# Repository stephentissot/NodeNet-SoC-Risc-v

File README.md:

# NodeNet SoC Risc-v — Colorlight i9 Multi-Node Embedded System

A complete RISC-V System-on-Chip (SoC) design for the Colorlight i9 FPGA board, featuring a PicoRV32 processor, Wishbone bus interconnect, persistent SPI flash storage, I2C peripherals, distributed RS485 multi-node communication via the NodeNet485 protocol, and a PLC runtime ready for relocatable object-file deployment.

## Overview

This project demonstrates a scalable embedded systems design on a cost-effective FPGA:
- **Processor**: PicoRV32 (32-bit RISC-V, bare-metal)
- **Clock**: 25 MHz
- **Memory**: 64 KiB ROM (stage0 bootloader) + 64 KiB RAM (stack/variables) + 8 MB SDRAM (runtime application/external data)
- **Peripherals**: D2 LED GPIO, RJ45 LED pulse controllers (`wb_led`), UART1 Modbus RTU master (`wb_modbus_master`), RS485 NodeNet485, I2C master, SDRAM controller
- **Communication**: NodeNet485 @ 1 Mb/s over RS-485 (multi-node capable)
- **Firmware**: C++17, bare-metal, newlib-nano
- **Validated boot path**: stage0 in ROM validates an image header in SPI flash, copies the payload to SDRAM, checks CRC, then jumps to the application entry point
- **Validated SDRAM path**: full firmware execution from SDRAM, 32-bit accesses, partial Wishbone writes, linker-placed `SDRAM_DATA` variables, and scratch-area self-tests

Current project status:
- **PLC Ready** with **V0 basic ISA**
- runtime point catalog with `pointDefsReq` / `pointStatesReq` browsing and pagination
- relocatable `objectFileV1` PLC upload, firmware-side link/load, linked-bytecode readback, and object-file readback
- 16 PLC slots with reboot persistence in the raw PLC flash package and automatic restore after boot
- OLED boot progress screen plus post-boot slot status screen
- ESP32 SPI coprocessor for local web API is in progress on the current branch; the shared SPI link, snapshot bootstrap, incremental state updates, and web UI runtime path are now working together on hardware, while broader validation and the MQTT bridge remain pending

## Features

### NodeNet PLC
- NodeNet PLC catalog browsing supports `pointDefsReq` and `pointStatesReq` with hierarchical paths of the form `deviceId.feature.pointId`.
- Point definitions can be created or updated with `pointUpsert`, and removed with `pointDelete`.
- Modbus-backed points are polled by the PLC runtime and exposed through the same NodeNet command surface.
- The PLC runtime publishes a shared SDRAM descriptor/value/status map, and PLC VM writes are consumed through the runtime write queue.
- Generic PLC deployment uses relocatable `objectFileV1` artifacts; the built-in `plcLoadReq` mirror helper remains available for fast validation.

PLC feature summary:
- Main feature status: PLC Ready with V0 basic ISA
- Runtime architecture: shared SDRAM PLC ABI, point runtime descriptors, value/status windows, slot loader/linker, persistent flash package restore at boot
- Deployment model: host builds relocatable `objectFileV1`, firmware links it against the live point catalog, loads it into one of 16 slots, and can persist the slot set for reboot restore
- Operating surface: NodeNet browse/update commands for point definitions and point states, PLC slot control/status points, raw PLC upload flow, linked-bytecode readback, and original object-file readback

PLC documentation index:
- Command surface and JSON examples: [README_NODENET_PLC_COMMANDS.md](README_NODENET_PLC_COMMANDS.md)
- PLC VM runtime architecture and ABI: [Documentation/plc_vm_spec_v1.md](Documentation/plc_vm_spec_v1.md)
- PLC assembly / object-file format: [Documentation/plc_assembly_spec_v1.md](Documentation/plc_assembly_spec_v1.md)
- ESP32 SPI bridge pinout and PlatformIO notes: [Documentation/esp32_spi_bridge_notes.md](Documentation/esp32_spi_bridge_notes.md)
- Firmware runtime and flash layout: [src/firmware/README.md](src/firmware/README.md)
- Stage0 boot flow and runtime handoff: [src/firmware/README_BOOT.md](src/firmware/README_BOOT.md)
- NodeNet transport details: [src/wbDevices/README_NODENET.md](src/wbDevices/README_NODENET.md)
- SPI flash persistence details: [src/wbDevices/README_FLASH.md](src/wbDevices/README_FLASH.md)
- Desktop PLC object-file tooling: [tools/BigSisterNodeNet.Plc/README.md](tools/BigSisterNodeNet.Plc/README.md)

### NodeNet Validation Snapshot (2026-08-20)
- Automatic heartbeat in HDL validated on hardware at ~10 s period.
- RX to local address validated (message accepted and decoded).
- TX path validated end-to-end.
- Runtime baud operation validated at both 115200 and 1 Mb/s.
- RX metadata is propagated end-to-end (`src`, `dst`, `broadcast`, `len`).
- Distinct PicoRV32 IRQs exist for broadcast vs unicast RX and are consumed through firmware callbacks.
- ROM stage0 now forwards the fixed IRQ vector at `0x00000004` to the SDRAM app IRQ entry.

### FlashDB Validation Snapshot (2026-08-13)
- Flash low-level test passes at boot (`[FLASH] LowLevel PASS`).
- FlashDB initialization passes (`[FDB] Ready`).
- Boot counter write path passes (`[FDB] boot cnt updated`).

### Hardware
- **Wishbone B.4 Bus** interconnect with 32-bit data, 32-bit address
- **PicoRV32 Core**: Open-source RISC-V ISA, ~6K LUT footprint
- **Memory Map**:
  - `0x00000000–0x0000FFFF`: 64 KiB boot ROM (stage0 bootloader)
  - `0x00010000–0x0001FFFF`: 64 KiB RAM (stack, BSS, heap)
  - `0x10000000`: D2 LED GPIO (1-bit output)
  - `0x10000004`: RJ45 LED0 (`wb_led` one-shot pulse)
  - `0x10000008`: RJ45 LED1 (`wb_led` one-shot pulse)
  - `0x10004000`: UART1 Modbus RTU master (`wb_modbus_master`)
  - `0x10005000`: I2C0 master (8 registers @ 4-byte stride)
  - `0x10006000`: NodeNet485 RS-485 mailbox (8 registers, 1 Mb/s)
  - `0x20000000–0x207FFFFF`: 8 MB SDRAM (runtime application image / framebuffer / logs)

### Peripherals
- **NodeNet485 Module** (`wb_nodenet.sv`):
  - Multi-node RS-485 communication protocol
  - Baud rate: runtime divisor (validated at 115200 and 1 Mb/s)
  - HDLC-style framing with parity bits and CRC
  - Mailbox-based Wishbone interface for TX/RX messages
  - Internal message buffering (no external SDRAM FIFO usage)
  - Anti-collision backoff (address-based delay)
  - Periodic heartbeat for node discovery
  - Priority-based transmission (LOW/NORMAL/HIGH)
  - Full C++ firmware API in `src/firmware/lib/nodenet/nodenet.h`
  - Supports unicast, broadcast, and heartbeat messages
  - Supports callback-driven broadcast / unicast reception on PicoRV32 IRQs
  - RX decode error reporting and TX scheduling status
  - Wishbone register interface (0x10006000)

- **I2C Module** (`wb_i2c.sv`):
  - Wraps Alex Forencich's `i2c_master_wbs_16` core
  - Hardware command + write + read FIFOs (32 entries each)
  - Configurable speed (default 100 kHz, up to 400 kHz @ 25 MHz)
  - Drives SCL/SDA open-drain (external 4.7 kΩ pullup required)
  - Wishbone address: 0x10005000

- **Modbus Master Module** (`src/modbus/wb_modbus_master.sv`):
  - Wishbone Modbus RTU master transaction engine
  - Uses shared `uart_simple.sv` UART core for wire-level TX/RX
  - Hardware-managed CRC16 (TX generation + RX validation)
  - Hardware-managed RTU frame gap detection (inter-frame silence)
  - Retries, timeout, and status/error flags exposed through MMIO
  - Firmware API in `src/firmware/lib/modbus/ModbusMaster.{h,cpp}`
  - Wishbone address: 0x10004000

- **SPI Flash Module** (`wb_flash.sv`, `spi_master.sv`):
  - Wishbone interface to on-board SPI flash (W25Q64, 8 MB)
  - Memory layout: 2 MB boot config (protected) + 12 KB point catalog + 4 KB compatibility gap + 128 KB PLC package + 124 KB FlashDB KV + 4 KB self-test scratch + app data
  - C++ firmware uses low-level page/sector API (`Flash`) plus FlashDB wrapper (`flashdb_port`)
  - Exposes the factory-programmed 64-bit Winbond UID as a stable ASCII device ID
  - Boot region protection: firmware rejects writes/erases to 0x000000–0x1FFFFF
  - Point catalog storage at 0x200000–0x202FFF (12 KB, 3 sectors)
  - Compatibility gap at 0x203000–0x203FFF (4 KB)
  - Persistent PLC package at 0x204000–0x223FFF (128 KB)
  - FlashDB KV partition at 0x224000–0x242FFF (124 KB)
  - Flash low-level self-test scratch at 0x243000–0x243FFF (4 KB)
  - Wishbone address: 0x10007000
  - See [src/wbDevices/README_FLASH.md](src/wbDevices/README_FLASH.md) for details
### Firmware
- **C++17 bare-metal** (`firmware/main.cpp`):
  - Compiled with `riscv-none-elf-g++` — no Arduino, no OS
  - `newlib-nano` provides `memcpy`/`strlen`/etc.
  - Dead code elimination (`-ffunction-sections -Wl,--gc-sections`)
  - Global C++ constructors called in `start.S` via `.init_array`
  - Final runtime image is linked for SDRAM via `link_app_sdram.ld`
  - Loaded by ROM-resident `boot_stage0` from SPI flash offset `0x244000`
  - Includes ArduinoJson 7 in freestanding mode, with an optional SDRAM-backed allocator for large JSON payloads
  - **NodeNet485 callback flow**: receives broadcast/unicast events through IRQ callbacks and defers heavy work to the main loop
  - D2 activity heartbeat: non-blocking software toggle every 500 ms

- **External SDRAM bring-up**:
  - Cold boot initialization now follows the generated LiteDRAM DFII sequence before the SDRAM user port is released
  - Firmware should still call `sdram_wait_ready()` before touching `SDRAM_DATA` objects or the JSON SDRAM pool

- See [src/firmware/README.md](src/firmware/README.md) for full peripheral usage guide.
- See [src/wbDevices/README_NODENET.md](src/wbDevices/README_NODENET.md) for protocol details.
- See [src/modbus/README.md](src/modbus/README.md) for Modbus RTU master details.
- See [src/wbDevices/README_FLASH.md](src/wbDevices/README_FLASH.md) for flash UID and device ID details.

## Building

### Prerequisites
- Yosys (synthesis)
- NextPNR (place & route)
- ecppack (bitstream generation)
- RISC-V GCC toolchain (`riscv-none-elf-gcc` ≥ 12, with C++ support)
- Make

> **After cloning**, fetch the u8g2 submodule:
> ```bash
> git submodule update --init
> ```

### Build Steps

```bash
# Full build (firmware + FPGA)
make all

# Stage0 bootloader only (ROM image)
make firmware-bootloader

# Alias: same stage0 ROM build as above
make firmware-build

# Build stage0 application image (SDRAM payload + header in SPI flash format)
make firmware-image

# SDRAM application ELF only
make -C src/firmware firmware-app-build

# Program firmware payload only in SPI flash (no FPGA rebuild)
make flash-fw

# If bootloader ROM startup / IRQ forwarding changed, reload the FPGA image too
make ram

# Optional: enforce openFPGALoader verify as fatal
make FW_STRICT_VERIFY=1 flash-fw

# Generate boot robustness test images (missing/size/crc fault injections)
make firmware-image-tests

# Run boot robustness fault scenarios
make flash-fw-test-missing
make flash-fw-test-crc
make flash-fw-test-size

# Firmware-only FPGA RAM update (ecpbram patch, fallback to make ram if needed)
make ram-fw

# Boot fault campaign checklist and expected blink codes
# See TEST.md

# FPGA synthesis only (requires pre-built firmware)
make

# Clean all artifacts
make clean

# Program FPGA SRAM (volatile)
make ram

# Program SPI flash (persistent, includes unlock during write)
make flash

# Manual flash protection control
make unlock-flash
make lock-flash
```

`make firmware-build` / `make firmware-bootloader` print stage0 ROM size telemetry on each build:
- ELF text/data/bss
- RAM usage (`.data + .bss`)
- HEX file size and payload bytes
- ROM usage (`payload / ROM_BYTES`, in %)

If payload exceeds ROM capacity, build stops with an explicit error.

CPU profile note:
- Default build is configured in fast mode for PicoRV32 in [src/top.sv](src/top.sv) with:
  - `.BARREL_SHIFTER(1)`
  - `.ENABLE_FAST_MUL(1)`
  - `.ENABLE_DIV(1)`
- To switch back to the normal/smaller CPU profile, set those three parameters to `0` in [src/top.sv](src/top.sv) and rebuild (`make clean; make`).

If OpenOCD flash programming fails on your setup, you can switch the flash
targets in `Makefile` to ecpdap. Reference commands:

```make
# ecpdap fallback examples (Colorlight i5/i9 style headers)
# flash:
# 	ecpdap flash unprotect
# 	ecpdap flash write build/top.config
#
# unlock-flash:
# 	ecpdap flash unprotect
#
# lock-flash:
# 	ecpdap flash protect
```

**Output**:
- `src/firmware/build/boot_stage0.hex` – Stage0 bootloader image (loaded into ROM, includes IRQ forward stub to the SDRAM app)
- `src/firmware/build/nodenet_riscv_app.img` – SDRAM app payload with stage0 header (written in SPI flash at `0x244000`)
- `build/top.bit` – FPGA bitstream (~300 KB)
- `build/top.json` – Netlist (debug/inspection)

## Memory Layout

```
Address Range               Size      Purpose
────────────────────────────────────────────────────────────
0x00000000–0x0000FFFF     64 KiB   Boot ROM (stage0 bootloader)
0x00010000–0x0001FFFF     64 KiB   RAM (stack, BSS, heap)
────────────────────────────────────────────────────────────
0x10000000                4 B      D2 LED GPIO (bit [0] = LED output)
0x10000004                4 B      RJ45 LED0 (`wb_led` control/status)
0x10000008                4 B      RJ45 LED1 (`wb_led` control/status)
0x10004000                32 B     UART1 Modbus RTU master (`wb_modbus_master`)
0x10005000                32 B     I2C0 master (8 regs @ 4-byte stride)
0x10006000–0x1000601F     32 B     NodeNet485 mailbox + LED config (RS485, 1 Mb/s)
0x10007000                32 B     SPI Flash controller (W25Q64)
────────────────────────────────────────────────────────────
0x20000000–0x207FFFFF     8 MB     SDRAM — Runtime app image + large buffers/logs
────────────────────────────────────────────────────────────
0x00000000–0x1FFFFF       2 MB     SPI Flash — FPGA boot config (PROTECTED)
0x200000-0x202FFF         12 KB    SPI Flash — Point catalog
0x203000-0x203FFF         4 KB     SPI Flash — Compatibility gap / reserved
0x204000-0x223FFF         128 KB   SPI Flash — Persistent PLC package
0x224000-0x242FFF         124 KB   SPI Flash — FlashDB KV partition
0x243000-0x243FFF         4 KB     SPI Flash — Flash low-level self-test scratch
0x244000–0x7FFFFF         5.73 MB  SPI Flash — Stage0 application image slot
```

## Boot Flow

1. FPGA configuration loads the SoC bitstream and the `wb_rom` contents containing `boot_stage0`.
2. Stage0 starts from `0x00000000`, initializes required peripherals, and reads the application header from SPI flash offset `0x244000`.
3. Stage0 validates header fields and CRCs, copies the application payload into SDRAM at `0x20000000`, then jumps to the image entry point.
4. PicoRV32 IRQ entry remains fixed at `0x00000004`; the ROM image forwards that vector to the SDRAM application IRQ entry at `0x20000004`.
5. The runtime firmware executes entirely from SDRAM, while SPI flash remains available for parameter storage, FlashDB, and firmware updates.
6. SDRAM self-tests used by the runtime stay inside a reserved scratch area so they do not overwrite the executing image.

## Device Pinout

### RS485 (NodeNet485 Protocol)
- **Pins**: G5 (RX), D16 (TX)
- **Baud Rate**: 1 Mb/s (fixed, configurable via UART parameter)
- **Protocol**: Multi-node RS-485 with HDLC framing, anti-collision, heartbeat
- **Transceiver**: Any RS-485 module with auto-switching (MAX485, SN65HVD11, etc.)
- **Multi-Node**: Up to 20 nodes on shared bus with address-based scheduling
- **Features**: Parity-encoded payload (2x expansion), XOR CRC, priority levels (LOW/NORMAL/HIGH), heartbeat
- **Connector topology**: 2x RJ45 in daisy-chain (IN/OUT), wired pin-to-pin between connectors

NodeNet RJ45 pinout (both connectors):

| RJ45 Pin | Signal |
|---|---|
| 1 | +12V |
| 2 | +12V |
| 3 | RS485 A |
| 4 | GND |
| 5 | GND |
| 6 | RS485 B |
| 7 | GND |
| 8 | GND |

### I2C (D18/D17 pins)
- **SCL**: D18
- **SDA**: D17
- Requires external 4.7 kΩ pullup resistors to 3.3 V on both lines
- Compatible with any I2C device: OLED, sensors, ADC, GPIO expanders…

### GPIO
- **D2 LED**: GPIO output at 0x10000000 (bit [0] = LED state)

### RJ45 LEDs (`wb_led`)
- **LED0 (F5)**: `0x10000004`
- **LED1 (E6)**: `0x10000008`
- Active-low wiring policy: GPIO high = LED OFF, GPIO low = LED ON.
- LPF enables pull-up on these pins for deterministic OFF level during startup.
- Write command bit0 triggers a non-blocking pulse (duration can be overridden by firmware).
- RJ45 LEDs are available through `wb_led` and can be used by application firmware when needed.

### NodeNet Activity LEDs (100% hardware)
- **RX activity LED (E5, green)**: default ON, pulses OFF when a valid frame is received.
- **TX activity LED (F4, orange)**: pulses ON when a transmission is queued.
- Active-low with pull-up: idle/high keeps LED OFF unless logic drives low.
- Blink duration is configured by firmware through NodeNet register `0x1000601C` (milliseconds).

### SPI Flash (W25Q64)
- **Pins**: R2 (CS), W2 (MOSI), V2 (MISO)
- **Clock**: Generated internally (10 MHz typical, no GPIO pin)
- **Capacity**: 8 MB (2 MB boot + 16 KB params + 256 KB FlashDB KV + ~5.73 MB app)
- **Boot Protection**: Firmware API rejects writes to 0x000000–0x1FFFFF
- **Parameter Region**: 0x200000–0x203FFF (raw/scratch area)
- **FlashDB KV Region**: 0x204000–0x243FFF (`nodenet_kv` partition)

## Firmware Examples

See **[src/firmware/README.md](src/firmware/README.md)** for a full guide with code examples for every peripheral.

### Quick-start: UART1 Modbus RTU master
```cpp
#include "ModbusMaster.h"

constexpr uint32_t MODBUS1_BASE = 0x10004000u;
constexpr uint8_t MODBUS_SLAVE = 0x01u;
ModbusMaster modbus1(MODBUS1_BASE);

int main() {
  modbus1.begin(9600, 500, 2);
  modbus1.setInterframeCharsQ1(14);

  uint16_t version = 0;
  if (modbus1.readHoldingRegisters(MODBUS_SLAVE, 0x8000, 1, &version)) {
    // 0x0064 => V1.00
  }

  for (;;) {
    // Toggle channel 1 (coil address 0)
    (void)modbus1.writeSingleCoil(MODBUS_SLAVE, 0x0000, true);
  }
}
```

### Quick-start: NodeNet echo
```cpp
#include <stdint.h>
#include "nodenet.h"

#define LED          (*(volatile uint32_t*)0x10000000)
constexpr uint32_t NODENET0_BASE = 0x10006000u;

int main() {
  NodeNet myNodeNet(NODENET0_BASE, 0x01, NODENET_PRIORITY_NORMAL, 200);
  for (;;) {
    if (myNodeNet.HasMessage()) {
      NodeNetMessage msg = myNodeNet.ReadMessage();
      if (msg.src_addr != 0) {
        myNodeNet.Send(msg.src_addr, msg.data, msg.len);
      }
      NodeNet::FreeMessage(msg);
    }
    LED ^= 1;
  }
}
```

### Quick-start: OLED via u8g2
```cpp
#include "u8g2_hal.h"

u8g2_t display;

int main() {
    u8g2_Setup_ssd1306_i2c_128x64_noname_f(
        &display, U8G2_R0,
        u8x8_byte_i2c_hw,
        u8x8_gpio_delay_hw);
    u8g2_InitDisplay(&display);
    u8g2_SetPowerSave(&display, 0);
    u8g2_ClearBuffer(&display);
    u8g2_SetFont(&display, u8g2_font_ncenB08_tr);
    u8g2_DrawStr(&display, 0, 12, "RISC-V SoC");
    u8g2_SendBuffer(&display);
    for (;;);
}
```

## Wishbone Bus Modules

See [src/wbDevices/README.md](src/wbDevices/README.md) for detailed documentation of each Wishbone peripheral module.

## Resource Usage

**Lattice LFE5U-45F-6BG381C** (Colorlight i9):
- Total LUTs: 45K
- Block RAM (DP16KD): 108 (each 16K bits)
- Current design:
  - PicoRV32: ~6K LUT
  - Interconnect: ~1K LUT
  - ROM (64 KiB): 32 blocks
  - RAM (64 KiB): 32 blocks
  - NodeNet485 transport + UART: ~300 LUT
  - SDRAM controller: ~400 LUT
  - GPIO: ~50 LUT
  - **Total: ~35% of available resources**

## Architecture

```
                   +----------------+
                   |   PicoRV32     |
                   +-------+--------+
                           |
                      Wishbone B4
                           |
      +--------+-----------+---------+--------+----------+-------+
      |        |           |         |        |          |       |
      wb_rom  wb_ram  wb_modbus_master  wb_nodenet wb_gpio wb_led wb_sdram wb_i2c
            |         |
            uart_simple  uart_simple
                 |
               NodeNet framing
        LED D2   RJ45 LEDs   M12L64322A  SSD1306   W25Q64
              |                    (8MB SDRAM) OLED
            RS485 Transceiver
                           |
                 Direct RS485 A/B/GND
                           |
                   Field Connectors
```

**Data Flow**:
1. **Power-up / stage0**: `wb_rom` exposes the 64 KiB ROM image containing `boot_stage0`, which loads and validates the SDRAM application stored in SPI flash.
2. **Runtime CPU** (PicoRV32): 32-bit RISC-V, 25 MHz clock, executing the main firmware from SDRAM after stage0 handoff.
3. **Wishbone B.4 Bus**: 32-bit address, 32-bit data, address decoder for memories and peripherals.
4. **Memory & I/O**:
  - `wb_rom`: 64 KiB boot ROM for stage0 only (0x00000000)
   - `wb_ram`: 64 KiB RAM (0x00010000)
  - `wb_sdram_litedram`: 8 MB SDRAM runtime memory window (0x20000000)
  - `wb_flash`: SPI flash control + persistence services (0x10007000)
  - `wb_modbus_master`: Modbus RTU master transport (0x10004000)
  - `wb_nodenet`: NodeNet485 mailbox transport (0x10006000)
  - `wb_gpio`: D2 GPIO output (0x10000000)
  - `wb_led`: RJ45 LED pulse controllers (0x10000004 / 0x10000008)
   - `wb_i2c`: I2C master with FIFOs (0x10005000)
5. **NodeNet Transport**: Mailbox-driven TX/RX framing, decode, and heartbeat scheduling.
6. **I2C Core**: Wraps Alex Forencich's `i2c_master_wbs_16` with Wishbone interface.
7. **RS485 Physical**: Transceiver converts CMOS <-> RS485 differential signaling.
8. **Field Wiring**: Each RS485 channel is exposed as direct A/B/GND connections.

## Planned Enhancements

- [x] 8 MB SDRAM controller (`wb_sdram_litedram.sv`) with LiteDRAM-generated core and runtime execution from SDRAM
- [x] I2C master (`wb_i2c.sv`) — Wishbone wrapper around verilog-i2c
- [x] u8g2 OLED display support (SSD1306 128×64 over I2C)
- [x] C++17 firmware with newlib-nano and dead-code elimination
- [x] SDRAM section in linker script (`sdram.h`, `SDRAM_DATA` macro)
- [ ] NodeNet485 mailbox transport with TX/RX framing and heartbeat (validation pending)
- [ ] UART1–4 implementation and testing
- [ ] RS485 direct connector mapping and labeling verification (A/B/GND)
- [ ] `wb_gpio` control bit for RS485 120R termination switch (74LVC1G66GW,125)
- [ ] Modbus V1 front-end: 4x RS485 modules with direct A/B/GND connectors per channel
- [ ] `wb_gpiopwm` peripheral + firmware API (PKLCS1212E4001-R1 buzzer)
- [ ] TMP117 board temperature sensor + firmware I2C driver/API
- [ ] Display validation: OLED over I2C and LCD over SPI (select final path after tests)
- [ ] Evaluate and select more robust 1 Mb/s transceivers for Modbus and NodeNet
- [ ] Dual Ethernet breakout using i9 onboard Broadcom PHYs (2x RJ45 with magnetics)
- [x] RJ45 LEDs integrated through `wb_led` at dedicated addresses
- [ ] Final RJ45 firmware policy (link/activity/status) for production runtime
- [ ] ESP32 module SPI coprocessor for web API and MQTT bridge (in progress: shared SPI link, HTTP app, websocket updates, and plcLink snapshot/resync path validated on hardware; MQTT bridge still pending)
- [ ] Power option study: use ESP32 module 3.3V rail vs dedicated 12V->3.3V buck
- [x] Modbus RTU master module + firmware driver (`wb_modbus_master` + `ModbusMaster`)
- [ ] Modbus RTU slave mode
- [ ] NodeNet JSON protocol wrapper (UART4)
- [ ] SPI slave interface for ESP32 co-processor
- [ ] SPI color LCD support (ST7789, 76x284) on Colorlight i9
- [ ] KNX integration with NCN5120 transceiver module
- [ ] Hardware-based CRC accelerator
- [ ] Real-time interrupt controller (RISC-V PLIC)

## Hardware Requirements

- **Colorlight i9 Board** with Lattice LFE5U-45F FPGA
- **USB-C Programmer** (e.g., openFPGALoader, oss-cad-suite)
- **RS485 Transceiver** modules (SN65HVD230, MAX483, etc.)
- **RS485 Field Connectors** (A/B/GND per channel)
- **SSD1306 OLED Module** (I2C, 128×32 or 128×64) + 4.7 kΩ pullup resistors

## Testing

```bash
# Program RAM (requires openFPGALoader)
make ram

# Program Flash (permanent)
make flash

# Explicit flash protection control (optional)
make unlock-flash
make lock-flash

# UART loopback test
# - Send "Hello" via USB-to-UART adapter
# - LED should blink
# - Characters echoed back
```

`make flash` now performs an explicit unlock step in the OpenOCD write command (`flash write_image erase unlock ...`) before erase/program.
`make lock-flash`/`make unlock-flash` call `flash protect ...` through OpenOCD; effectiveness/persistence depends on driver support for the target flash path.

## References

- [PicoRV32 GitHub](https://github.com/YosysHQ/picorv32)
- [Verilog UART IP (Alex Forencich)](https://github.com/alexforencich/verilog-uart) – Core UART module used in wb_uart.sv
- [Verilog I2C IP (Alex Forencich)](https://github.com/alexforencich/verilog-i2c) – Core I2C module used in wb_i2c.sv
- [u8g2 Graphics Library](https://github.com/olikraus/u8g2) – OLED display driver (git submodule)
- [Wishbone B.4 Specification](https://cdn.opencores.org/downloads/wbspec_b4.pdf)
- [LFE5U FPGA Datasheet](https://www.latticesemi.com/en/Products/FPGAs/ECP5)
- [RISC-V Unprivileged ISA Manual](https://riscv.org/specifications/)

## License

See [LICENSE](LICENSE) file.

## Author

**Stephen Tissot**  
Industrial IoT / FPGA Engineering  
https://github.com/stephentissot

---

**Status**: Prototype / Active Development  
**Last Updated**: 2026-08-18

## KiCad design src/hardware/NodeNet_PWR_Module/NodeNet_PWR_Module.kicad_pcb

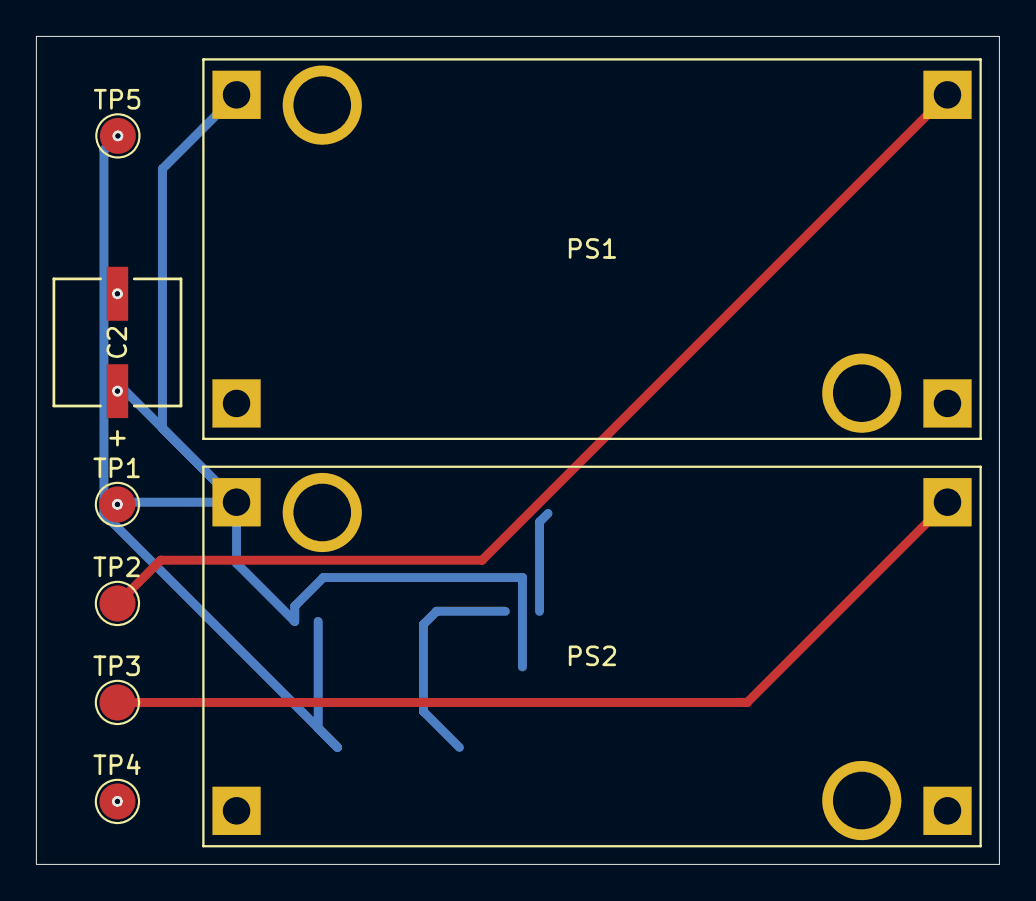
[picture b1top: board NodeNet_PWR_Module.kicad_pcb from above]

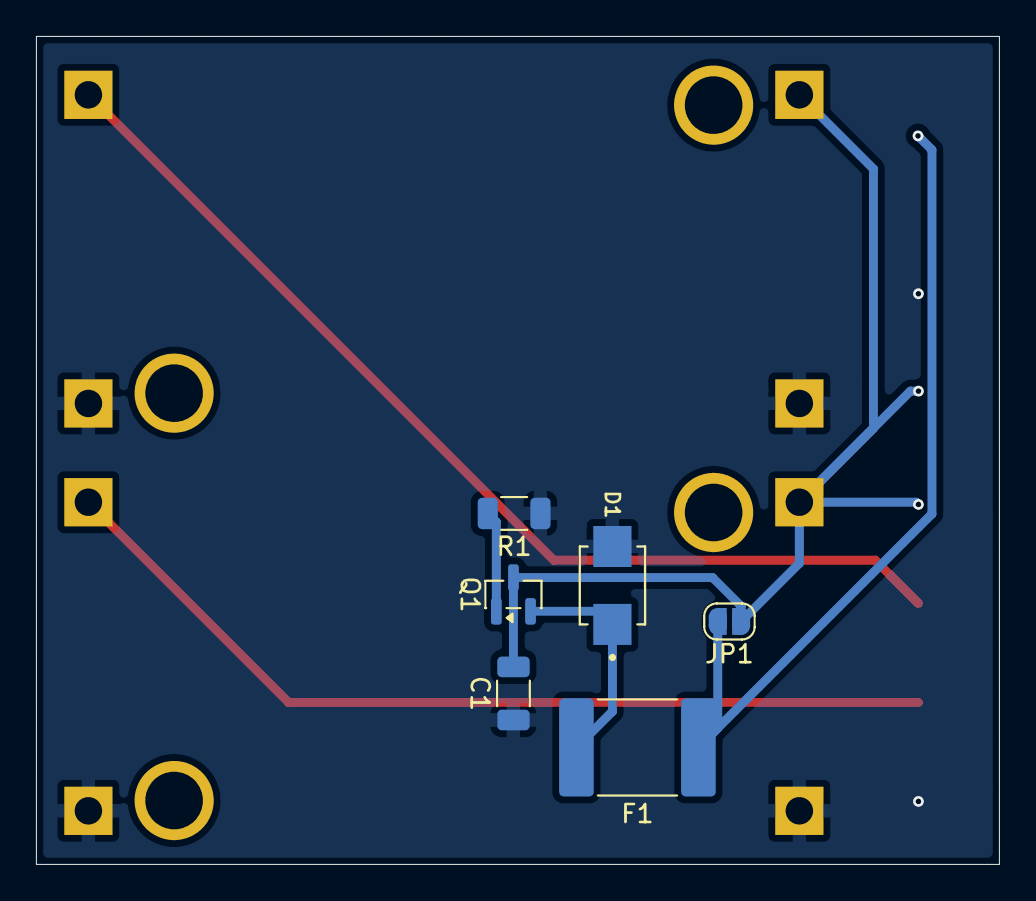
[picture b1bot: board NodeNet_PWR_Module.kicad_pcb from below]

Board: 2 copper layers, 53.5 x 46.0 mm, 14 parts (6 on the bottom side), 7 nets.

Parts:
C1: 100nF 50V; C_1206_3216Metric
C2: 100 uF 25V; PCAP_6.3x7.7-ELECT_NCA
D1: SMBJ15A
F1: MF-LSMF185X-2; Fuse_2920_7451Metric
JP1: ByPass; SolderJumper-2_P1.3mm_Open_RoundedPad1.0x1.5mm
PS1: 12V 5V buck converter; CONV_MC00100
PS2: 12V 3.3V buck converter; CONV_MC00100
Q1: AO3407A; SOT-23
R1: 100K; R_1206_3216Metric
TP1: 12V; TestPoint_Pad_D2.0mm
TP2: 5V; TestPoint_Pad_D2.0mm
TP3: 3.3V; TestPoint_Pad_D2.0mm
TP4: GND; TestPoint_Pad_D2.0mm
TP5: 12VIn; TestPoint_Pad_D2.0mm

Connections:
/3V3: PS2.OUT+, TP3.1 (1_1)
/5V: PS1.OUT+, TP2.1 (1_1)
/12V: C1.2, C2.1, JP1.1 (A), PS1.IN+, PS2.IN+, Q1.3 (D), TP1.1 (1_1)
/Ext 12V: F1.1, JP1.2 (B), TP5.1 (1_1)
/Ext GND: C1.1, C2.2, D1.A, PS1.IN-, PS1.OUT-, PS2.IN-, PS2.OUT-, R1.1, TP4.1 (1_1)
unnamed: Q1.1 (G), R1.2
unnamed: D1.C, F1.2, Q1.2 (S)
